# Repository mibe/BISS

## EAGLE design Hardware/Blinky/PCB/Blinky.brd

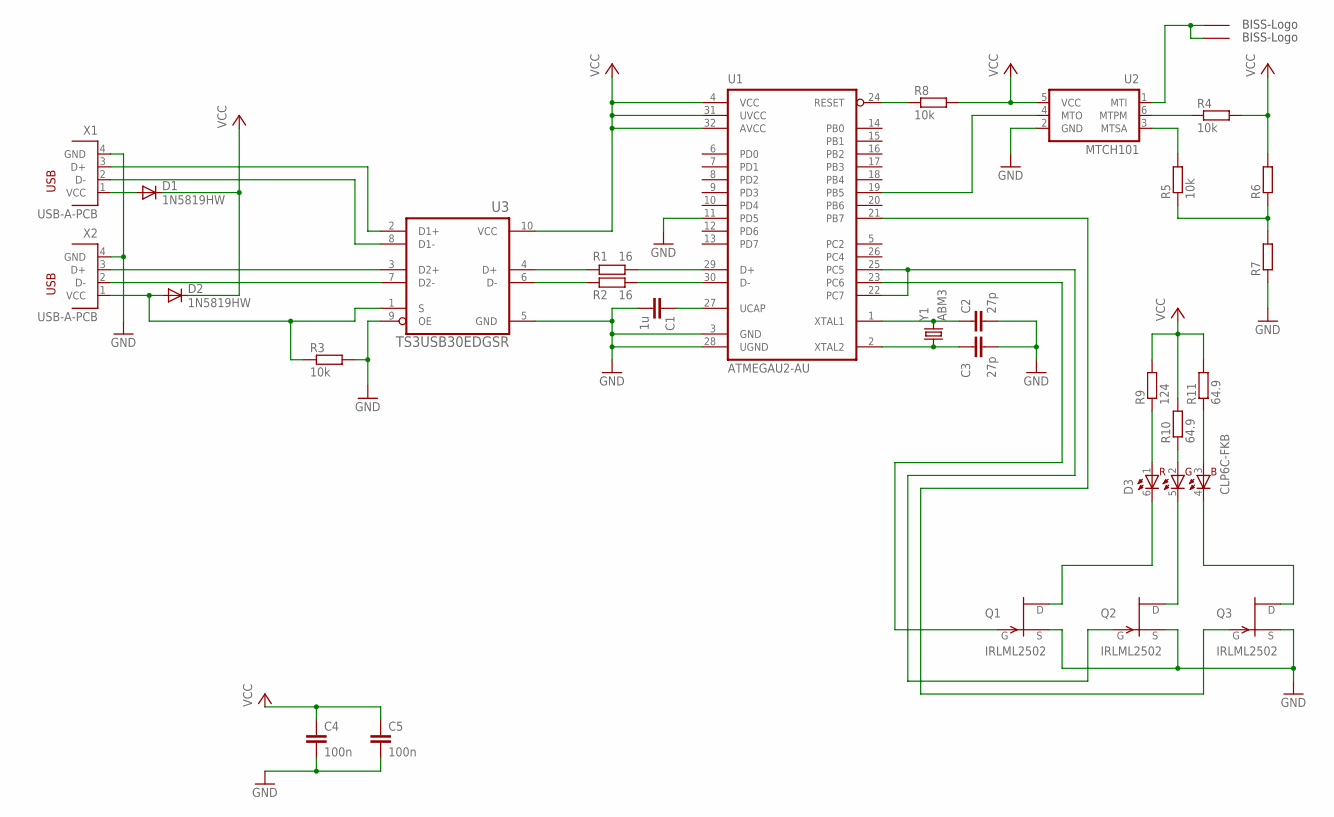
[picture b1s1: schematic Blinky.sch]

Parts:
C1: 1u; C0805
C2, C3: 27p; C0805
C4, C5: 100n; C0805
D1, D2: 1N5819HW; SOD123
D3: CLP6C-FKB; PLCC-6
Q1, Q2, Q3: IRLML2502; SOT23
R1, R2: 16; R0805
R3, R4, R5, R8: 10k; R0805
R6, R7: R-EU_R0805; R0805
R9: 124; R0805
R10, R11: 64.9; R0805
U1: ATMEGAU2-AU; TQFP32-08
U2: MTCH101; SOT23-6
U3: TS3USB30EDGSR; VSSOP-10
U$1, U$2: LOGO
X1, X2: USB-A-PCB
Y1: ABM3

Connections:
D1+: U3.2 (D1+), X1.3 (D+)
D1-: U3.8 (D1-), X1.2 (D-)
D2+: U3.3 (D2+), X2.3 (D+)
D2-: U3.7 (D2-), X2.2 (D-)
D+_CON: R1.1, U3.4 (D+)
D+_MIC: R1.2, U1.29 (D+)
D-_CON: R2.1, U3.6 (D-)
D-_MIC: R2.2, U1.30 (D-)
GND: C1.2, C2.2, C3.2, C4.2, C5.2, Q1.2 (S), Q2.2 (S), Q3.2 (S), R3.2, R7.1, U1.3 (GND), U1.11 (PD5), U1.28 (UGND), U2.2 (GND), U3.5 (GND), U3.9 (OE), X1.4 (GND), X2.4 (GND)
GND_LED_B: D3.4, Q3.3 (D)
GND_LED_G: D3.5, Q2.3 (D)
GND_LED_R: D3.6, Q1.3 (D)
LED_B: Q3.1 (G), U1.21 (PB7)
LED_G: Q2.1 (G), U1.22 (PC7), U1.25 (PC5)
LED_R: Q1.1 (G), U1.23 (PC6)
unnamed: R4.1, U2.6 (MTPM)
unnamed: R5.2, U2.3 (MTSA)
unnamed: R5.1, R6.1, R7.2
RESET: R8.1, U1.24 (RESET)
TOUCH: U1.19 (PB5), U2.4 (MTO)
TOUCH_PAD: U2.1 (MTI), U$1.P$1, U$2.P$1
UCAP: C1.1, U1.27 (UCAP)
VCC: C4.1, C5.1, D1.C, D2.C, R4.2, R6.2, R8.2, R9.2, R10.2, R11.2, U1.4 (VCC), U1.31 (UVCC), U1.32 (AVCC), U2.5 (VCC), U3.10 (VCC)
VUSB1: D1.A, X1.1 (VCC)
VUSB2: D2.A, R3.1, U3.1 (S), X2.1 (VCC)
V_LED_B: D3.3, R11.1
V_LED_G: D3.2, R10.1
V_LED_R: D3.1, R9.1
XTAL1: C2.1, U1.1 (XTAL1), Y1.2
XTAL2: C3.1, U1.2 (XTAL2), Y1.1

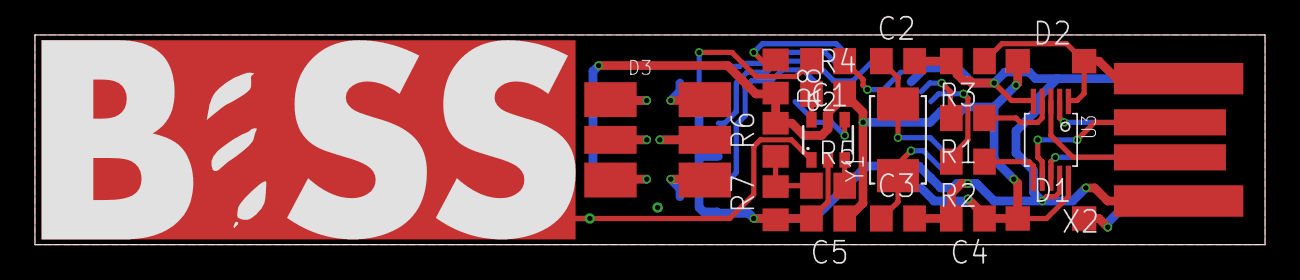
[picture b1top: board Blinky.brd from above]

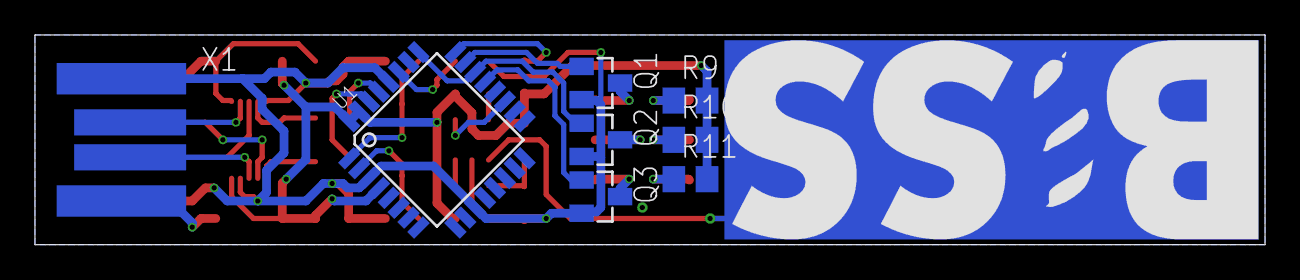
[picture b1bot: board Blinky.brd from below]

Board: 2 copper layers, 70.4 x 12.0 mm, 30 parts (9 on the bottom side), 30 nets.

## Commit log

2016-12-21 First bits of the network stack.
2016-12-29 Implemented the receiving side.
2017-01-22 Some restructuring
2017-01-23 New message type
2017-01-23 The very first bits of a sending application called "Boss".
2017-01-23 Don't display a message box, but instead change the text of the button.
2017-01-23 The very first bits of a simple receiving application called "PopUp".
2017-01-26 Added the solution file.
2017-02-26 Added LUFA version 151115
2017-02-28 Set the ReuseAddress socket option to support running multiple receivers at the same time on the same port.
2017-03-15 Initial commit using the GenericHID code from LUFA's lowlevel demos.
2017-03-19 The Sender now needs a IP address specified, on which the UDP socket should be binded to.
    This is the groundwork for sending the BISS message on more than one interfaces (see #4 for details).
2017-03-19 New class InterfaceSender for transmitting the BISS packet over all network interfaces.
    This fixes #4.
2017-03-19 Use the InterfaceSender to send on all network interfaces.
2017-03-19 Correct settings in makefile for BISS.Blinky.
2017-03-21 Removed unused code:
    - XMEGA specific stuff
    - LED stuff
    - USB events
2017-03-21 USB device descriptor settings like VID/PID.
    Using pid.codes' test VID/PID for now.
2017-03-22 Renamed GenericHID.* to Blinky.*
2017-03-22 First bits of the display driver.
2017-03-27 Store user settings in EEPROM.
    The blinking frequency and the LED color is currently saved.
2017-04-09 Bugfix: blue LED was not disabled correctly.
    PB7 is on port B and not on port C of course.
2017-04-14 Renamed Frequency to BlinkInterval.
    The blink interval is not exactly a frequency in Hertz. The name interval fits better.
2017-04-14 Default settings as symbolic constants.
2017-04-16 Blink algorithm.
    This is using Timer0 in pseudo CTC mode.
    CTC is implemented in software by using the timer overflow interrupt.
    The algorithm is also using a GPIO register for storing a status bit.
2017-04-20 The settings are now globalized.
    The Settings.h file contains a global variable "settings" now, usable for all other functions. Previously Display.c / Blinker.c had their own variables for storing settings.
    This saves about 200 Bytes of flash memory.
2017-04-20 Moved counter variable into ISR.
2017-04-22 More sensible settings defaults.
2017-04-23 Functions for returning the current state of the settings and to clear them.
    This information can be used by the controlling application on the host computer to inform the user that the device is not configured.
2017-04-25 The first four commands from the USB host to the device are implemented.
    That is the trigger command and the save, set and reset settings command.
2017-04-26 CMD_GetSettings implemented.
2017-05-09 Implemented the command to jump to the bootloader.
2017-05-15 Monitor the pin connected to the touch sensor to disable the blinker.
2017-05-15 The touch sensor input can now be disabled when specified by the host.
2017-10-30 Don't use the Pin Change Interrupt to monitor the touch sensor output.
    That thing didn't work properly, because after a triggered interrupt, data send from the USB host wasn't received. I don't know why, and after two hours of debugging I decided to ditch that interrupt.
2017-10-30 The blinker algorithm performs consistent with multiple calls of Disable() / Enable().
    The inconsistency was caused by not initialized status variables.
2017-11-05 New settings entry for storing the blinker timeout value.
2017-11-05 Implement the timeout logic in the blinker code.
2017-11-05 Removed not needed function:
    HID control requests are not used.
2017-11-05 The timeout feature of the blinker can be en-/disabled.
    Bit 2 of Byte 2 of the report is used for that.
2017-11-11 Introduce a sync byte, which is sent by the host and copied to the reply packet.
2017-11-12 Added an auxiliary output, which is high when the blinker is active and low if it isn't.
2017-11-26 First rough cut of the hardware library described in issue #7.
    It currently fully supports the BISS.Blinky device.
2017-11-26 Support for setting a communication timeout between the USB host & device.
2017-11-26 New command for turning off a triggered device.
2017-11-28 The Device class is now thread-safe.
2017-11-28 Provide an value of zero for the TriggerFlags enum.
2017-11-28 Comments, comments and comments again.
2017-11-28 Event stuff:
    * Raise the event in an overrideable OnRemoved method.
    * The Removed event was not public.
2017-11-28 The default communications timeout is 100 ms.
2017-11-29 Bugfix: The Connected property used the wrong HidDevice property.
2017-11-29 Bugfix: The Removed event was not raised in the underlying library.
2017-11-29 New command for sending and receiving a heartbeat signal.
2017-12-10 Implement IEquatable<> for Settings class.
2017-12-10 Refactored the GetSettings / SetSettings method to a property.
2018-02-05 Schematic for the BISS Blinky.
    Still missing: The correct resistor values for the touch sensor and the sensor pad itself.
2018-03-04 Most of the PCB layout is done.
    Still missing is the touch sensor disguised as logo (hello issue #10).
2018-03-07 Changed the series resistance on the USB lines to 16 Ohm.
    The USB switch U3 is introducing some additional resistance in the on state.
2018-04-09 Say hello to the logo!
    This finally closes #10.
2018-04-15 Transformed the BISS logo into an Eagle package.
    Boy, that took some doing. I hope this works...
2018-04-16 Imported the BISS logo into the Blinky PCB.
    This also determined the final size of the PCB.
2018-04-21 Added ground pour on both sides and moved some traces and vias around.
2018-04-21 No cream on the logo pad.
2018-05-06 Gerber & Excellon files which were sent to the fab house
2018-06-28 Someone (read: I) forgot the pull-down resistors at the gates at the MOSFETs. 😳
    This bug is fixed in software: The timer which provides the PWM signal to the gate is stopped when the LED should be off and started again when it should be on again. The pin is at all times configur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
2018-06-28 Firmware license information
2018-06-28 Moved LUFA into firmware directory.
